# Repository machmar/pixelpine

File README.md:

# PixelPine — a 7 cm PCB Christmas tree with 240 charlieplexed LEDs

KTE Project 1 · design-for-manufacture study · rev A · 2026-09-23

A chubby, cute, 70 mm tall PCB tree covered in **240 warm-white 0603 LEDs** on a 2.12 mm grid. The LEDs are
charlieplexed on 16 pins of a **$0.13 Puya PY32F003** (Cortex-M0+, 64 KB flash) with software PWM. It runs from USB-C and slots into a
PCB stand fin. The tree is a character, **Pine**, whose job is showing light shows. He's bad at it: he daydreams,
naps, gets grumpy and gets excited to show you things. You interact with him through the capacitive star, which
senses tap, pet, press, a front-and-back squeeze and tickles. The product firmware runs on the first boards and
matches the simulator frame for frame ([`firmware/pixelpine/`](firmware/pixelpine/README.md)).
Landed cost ≈ **€3.2 at 1 000 pcs, €2.0 at 10 000 pcs**; suggested shelf price **€12.90**.

**Try Pine in your browser: [machmar.github.io/pixelpine](https://machmar.github.io/pixelpine/)** (the animation simulator).

| Front | Back |
|---|---|
|  |  |

## Deliverables

| You asked for | Where |
|---|---|
| Schematic | [`hardware/pixelpine_schematic.pdf`](hardware/pixelpine_schematic.pdf) · KiCad 10 project [`hardware/pixelpine.kicad_pro`](hardware/pixelpine.kicad_pro) (ERC: 0 errors, 0 warnings) |
| PCB shape and layout | [`hardware/pixelpine.kicad_pcb`](hardware/pixelpine.kicad_pcb): outline, stand fin, all 267 parts (+2 logo marks) placed with nets, silkscreen, CE/WEEE marks, **routed on 2 layers** (Freerouting, then finished by hand in KiCad: GND pour on both layers, 142 vias). DRC: 0 unconnected, schematic parity 0 issues; 2 cosmetic *starved thermal* notes (see the order guide). The LEDs sit in a routing-friendly arrangement: see [LED arrangement](#led-arrangement) |
| BOM (LCSC / JLCPCB) | [`docs/bom.md`](docs/bom.md) · JLC upload files [`hardware/production/jlc_bom.csv`](hardware/production/jlc_bom.csv), [`jlc_cpl.csv`](hardware/production/jlc_cpl.csv) |
| **Order files** | [`hardware/production/`](hardware/production/README.md): Gerber + drill zips for the tree (PCB + assembly) and the stand fin (bare PCB), BOM/CPL, 3D previews, and an order guide with every JLC setting and what to check in the placement preview |
| PC app to preview the animations | [`simulator/index.html`](simulator/index.html), live at [machmar.github.io/pixelpine](https://machmar.github.io/pixelpine/) (published from `simulator/` by `.github/workflows/pages.yml`): open it in any browser; works offline apart from fonts. Pine runs live: touch his star (hover / click / hold / shift / ctrl / fast clicks) and watch his feelings change. Preview mode plays any show, face or transition. Includes an electrical model of the charlieplex (current sag, PWM depth, refresh, pin current) |
| Pine: character, faces, transitions, gestures | [`docs/animations.md`](docs/animations.md): behaviour state machine, emotions, 15 light shows, 16 faces, 6 transitions, touch gestures, RAM/flash budget |
| Market analysis | [`docs/market-analysis.md`](docs/market-analysis.md) |
| EU certification setup | [`docs/eu-compliance/`](docs/eu-compliance/README.md): applicability matrix, EMC test plan, technical file + risk assessment, DoC template, labels and leaflet (EN/CZ) |
| Final price analysis incl. assembly | [`docs/cost-analysis.md`](docs/cost-analysis.md), generated by [`docs/cost_model.py`](docs/cost_model.py) |
| Connectivity & power consumption | [`docs/power-and-connectivity.md`](docs/power-and-connectivity.md) |
| Product firmware (beyond the brief) | [`firmware/pixelpine/`](firmware/pixelpine/README.md): the simulator ported to C and running on the board: **59 KB of 63 KB flash, 7.0 KB of 8 KB RAM**, 50 fps, 122 Hz 10-bit BCM scan. Checked frame by frame against the simulator's own JavaScript: Pine's state machine and emotions identical in every whole-Pine test, LED levels within 1 step of 255 on ≥ 99.99 % of LED-frames there (per show: 93–100 %, fireflies lowest). Touch calibrated on the board; room-light sensing isn't possible on rev A (and how rev B fixes it); a whole-tree touch field was tried and dropped (why). Flashing: [`firmware/flash/`](firmware/flash/README.md) |
| Firmware fit check | [`firmware/sizetest/`](firmware/sizetest/README.md): real compile of all shows, faces, brain and drivers for both MCUs. The original CH32V003 overflowed (20.9 KB of 16 KB), so the MCU was switched to the PY32F003F18P6: **17.2 KB of 64 KB flash (27 %), 1.9 KB of 8 KB RAM (23 %)**, built with the Arm GNU Toolchain. See [`docs/animations.md`](docs/animations.md#firmware-budget-measured-by-a-test-compile) |
| Design spec | [`docs/superpowers/specs/2026-09-23-pixelpine-design.md`](docs/superpowers/specs/2026-09-23-pixelpine-design.md) |
| All docs as PDF | [`docs/pdf/PixelPine-documentation.pdf`](docs/pdf/PixelPine-documentation.pdf): everything above in one linked PDF (cover, contents), plus one PDF per doc in [`docs/pdf/`](docs/pdf/). Regenerate with `python docs/export_pdfs.py` after editing a doc |

## Key numbers

| | |
|---|---|
| LEDs | 240 × XL-1608WWC-06 (0603, 2500–3000 K) at 45°, 2.12 mm pitch |
| MCU | Puya PY32F003F18P6 (TSSOP-20, pinout 1, 24 MHz internal oscillator): 16 charlieplex lines (incl. SWD pins and BOOT0) + ADC touch star (PA7) + NRST; SWD programming |
| Character | 6 emotions (energy, focus, mood, annoyance, excitement, bond in flash), 16 faces, 6 transitions |
| Parts | 263 placements, 8 line items, 552 SMD joints, single-sided |
| PCB | 2-layer FR-4 1.6 mm, LF-HASL, JLC standard process (0.10 mm tracks and spaces at the narrowest, 0.3 / 0.4 mm vias); 1658 track segments (1991 mm), 142 vias, GND pour on both layers, 0 unrouted. Tree 50.5 × 70 mm, stand fin 36 × 10 mm |
| Supply | USB-C 5 V, 3–12 mA typical (≈ 7 mA average), 19 mA max → ≤ 0.1 W |
| Light | ≈ 2 lm total, so outside the EU light-source ecodesign/energy-label scope |
| Pin current | ≤ 16.2 mA per GPIO by design (20 mA rated) |
| PWM | 8-bit binary-code modulation, 16 phases, 122 Hz refresh (the product firmware: 10-bit, same refresh) |
| CE route | EMC 2014/30/EU (EN IEC 55015 + EN 61547) + RoHS; GPSR, WEEE, PPWR, REACH obligations |

## LED arrangement

The 240 LED positions are a fixed 2.12 mm grid, but *which* anode/cathode pair sits at which position is a free choice,
and it decides whether the board can be routed at all. The first version interleaved the pairs (`anode = n mod 16`),
which leaves every one of the 480 LED pads as an island of its own, and Freerouting stalled with 76 connections still
open after 87 minutes.

The 45° LEDs form a "brick" lattice with only ~0.55 mm between neighbouring pads. If two neighbouring pads are on the
same line net, a tiny F.Cu bridge joins them for free, so a net can be a few big copper islands instead of 30 loose
pads. [`hardware/scripts/optimize_leds.py`](hardware/scripts/optimize_leds.py) (simulated annealing, C core in
`optimize_leds.c`) arranges the 240 pairs for exactly that: 480 separate pads became 141 islands, only the links between
islands need real wiring, and the board routes on **2 layers** in about 2 minutes (it also stopped needing the 4 layers
that the old arrangement was thought to need). The result is [`hardware/led_assignment.json`](hardware/led_assignment.json),
committed; `geometry.py` reads it, so the schematic, PCB, simulator map and firmware tables all follow from it. Every
LED keeps the same orientation; the optimiser can also turn LEDs round by 180° (`--flip`) for ~15 % fewer islands, but
that wasn't needed.

Side effect: neighbouring LEDs now sometimes share an anode line (17 % of the LED pairs closer than 3.2 mm, against
6 % with the old interleaving), so a lit blob loads some scan phases harder than before. The numbers are in
[`docs/power-and-connectivity.md`](docs/power-and-connectivity.md#which-leds-share-a-phase).

## Regenerating the hardware

> **Since 2026-10-01 the board is finished by hand in KiCad** (GND pour, extra vias). `build_all.py` would
> regenerate it from the scripts and drop those edits, so it now stops unless you pass `--regenerate`. For order
> files run `export_gerbers.py` (KiCad's Python) and `export_fab.py`; see
> [`hardware/production/README.md`](hardware/production/README.md).

Everything in `hardware/` was generated from one geometry module, so it stays consistent:

```bash
python hardware/scripts/build_all.py
```

`geometry.py` (outline, LED grid, charlieplex map from `led_assignment.json`) → `gen_footprints.py` → `gen_sch.py`
(+ ERC, netlist check) → `gen_pcb.py` (KiCad's bundled Python) → `route.py` (Freerouting, ~2-5 min; if connections stay
open it routes again from scratch, up to 4 runs) → DRC and parity → 3D renders → JLC BOM/CPL. It also refreshes
`simulator/led_map.js`, so the simulator always shows the real LED positions. After editing the outline, run
`python hardware/scripts/geometry.py --search` and paste the new pitch into `GRID_PITCH`, then
`python hardware/scripts/optimize_leds.py` (needs a C compiler, 10–20 min) to re-arrange the LEDs for the new grid.
The firmware's per-LED tables come from the same map: `python firmware/pixelpine/gen_tables.py`, then
`python firmware/pixelpine/build.py flash` builds and programs a board, and `python firmware/pixelpine/test/compare.py`
checks the firmware against the simulator.

## Open items before ordering

Order files are ready: [`hardware/production/README.md`](hardware/production/README.md). At order time, check
LCSC stock for the 240 LEDs per board and look at the LED polarity and U1 pin 1 in JLC's placement preview.

1. **Firmware: done on the first board** (2026-11-03): it powers up at 4.97 V with no short, flashes through a
   J-Link ([`firmware/flash/`](firmware/flash/README.md)) and runs Pine ([`firmware/pixelpine/`](firmware/pixelpine/README.md)).
   Still open: touch thresholds measured on one board and one hand (measure a batch); the EMC worst-case and
   production-test firmware builds.
2. **Room light can't be sensed on rev A**: in a full charlieplex every LED has an anti-parallel twin, so no LED can
   work as a photodiode, and Pine stays in "lights on" mode. Rev B fix at no cost: leave one LED unpopulated
   ([`firmware/pixelpine/README.md`](firmware/pixelpine/README.md#room-light)).
3. **Hover isn't detectable** with the star electrode (a finger 1 cm away is below the noise); tap, pet, press,
   squeeze and tickle work.
4. **No whole-tree touch on rev A**: the LED lines can pick up the mains hum a finger carries, but only on a
   mains-tied supply (strong on a laptop, weak on a wall charger, nothing on a powerbank), so it was dropped after
   five experiments ([`firmware/pixelpine/README.md`](firmware/pixelpine/README.md#touch-field-tried-dropped)). The star
   is the touch control.

Done: PCB routed on 2 layers (LED arrangement optimised for it, DRC clean), manufacturer name, address (Jehličková 240, 240 24 Stromečkov: made up for the school project, replace it with the
registered address for a real product) and e-mail on the product, U1 and J1 placement orientation checked, MCU choice final
(PY32F003F18P6, kept over the cheaper F002A for firmware-update headroom).

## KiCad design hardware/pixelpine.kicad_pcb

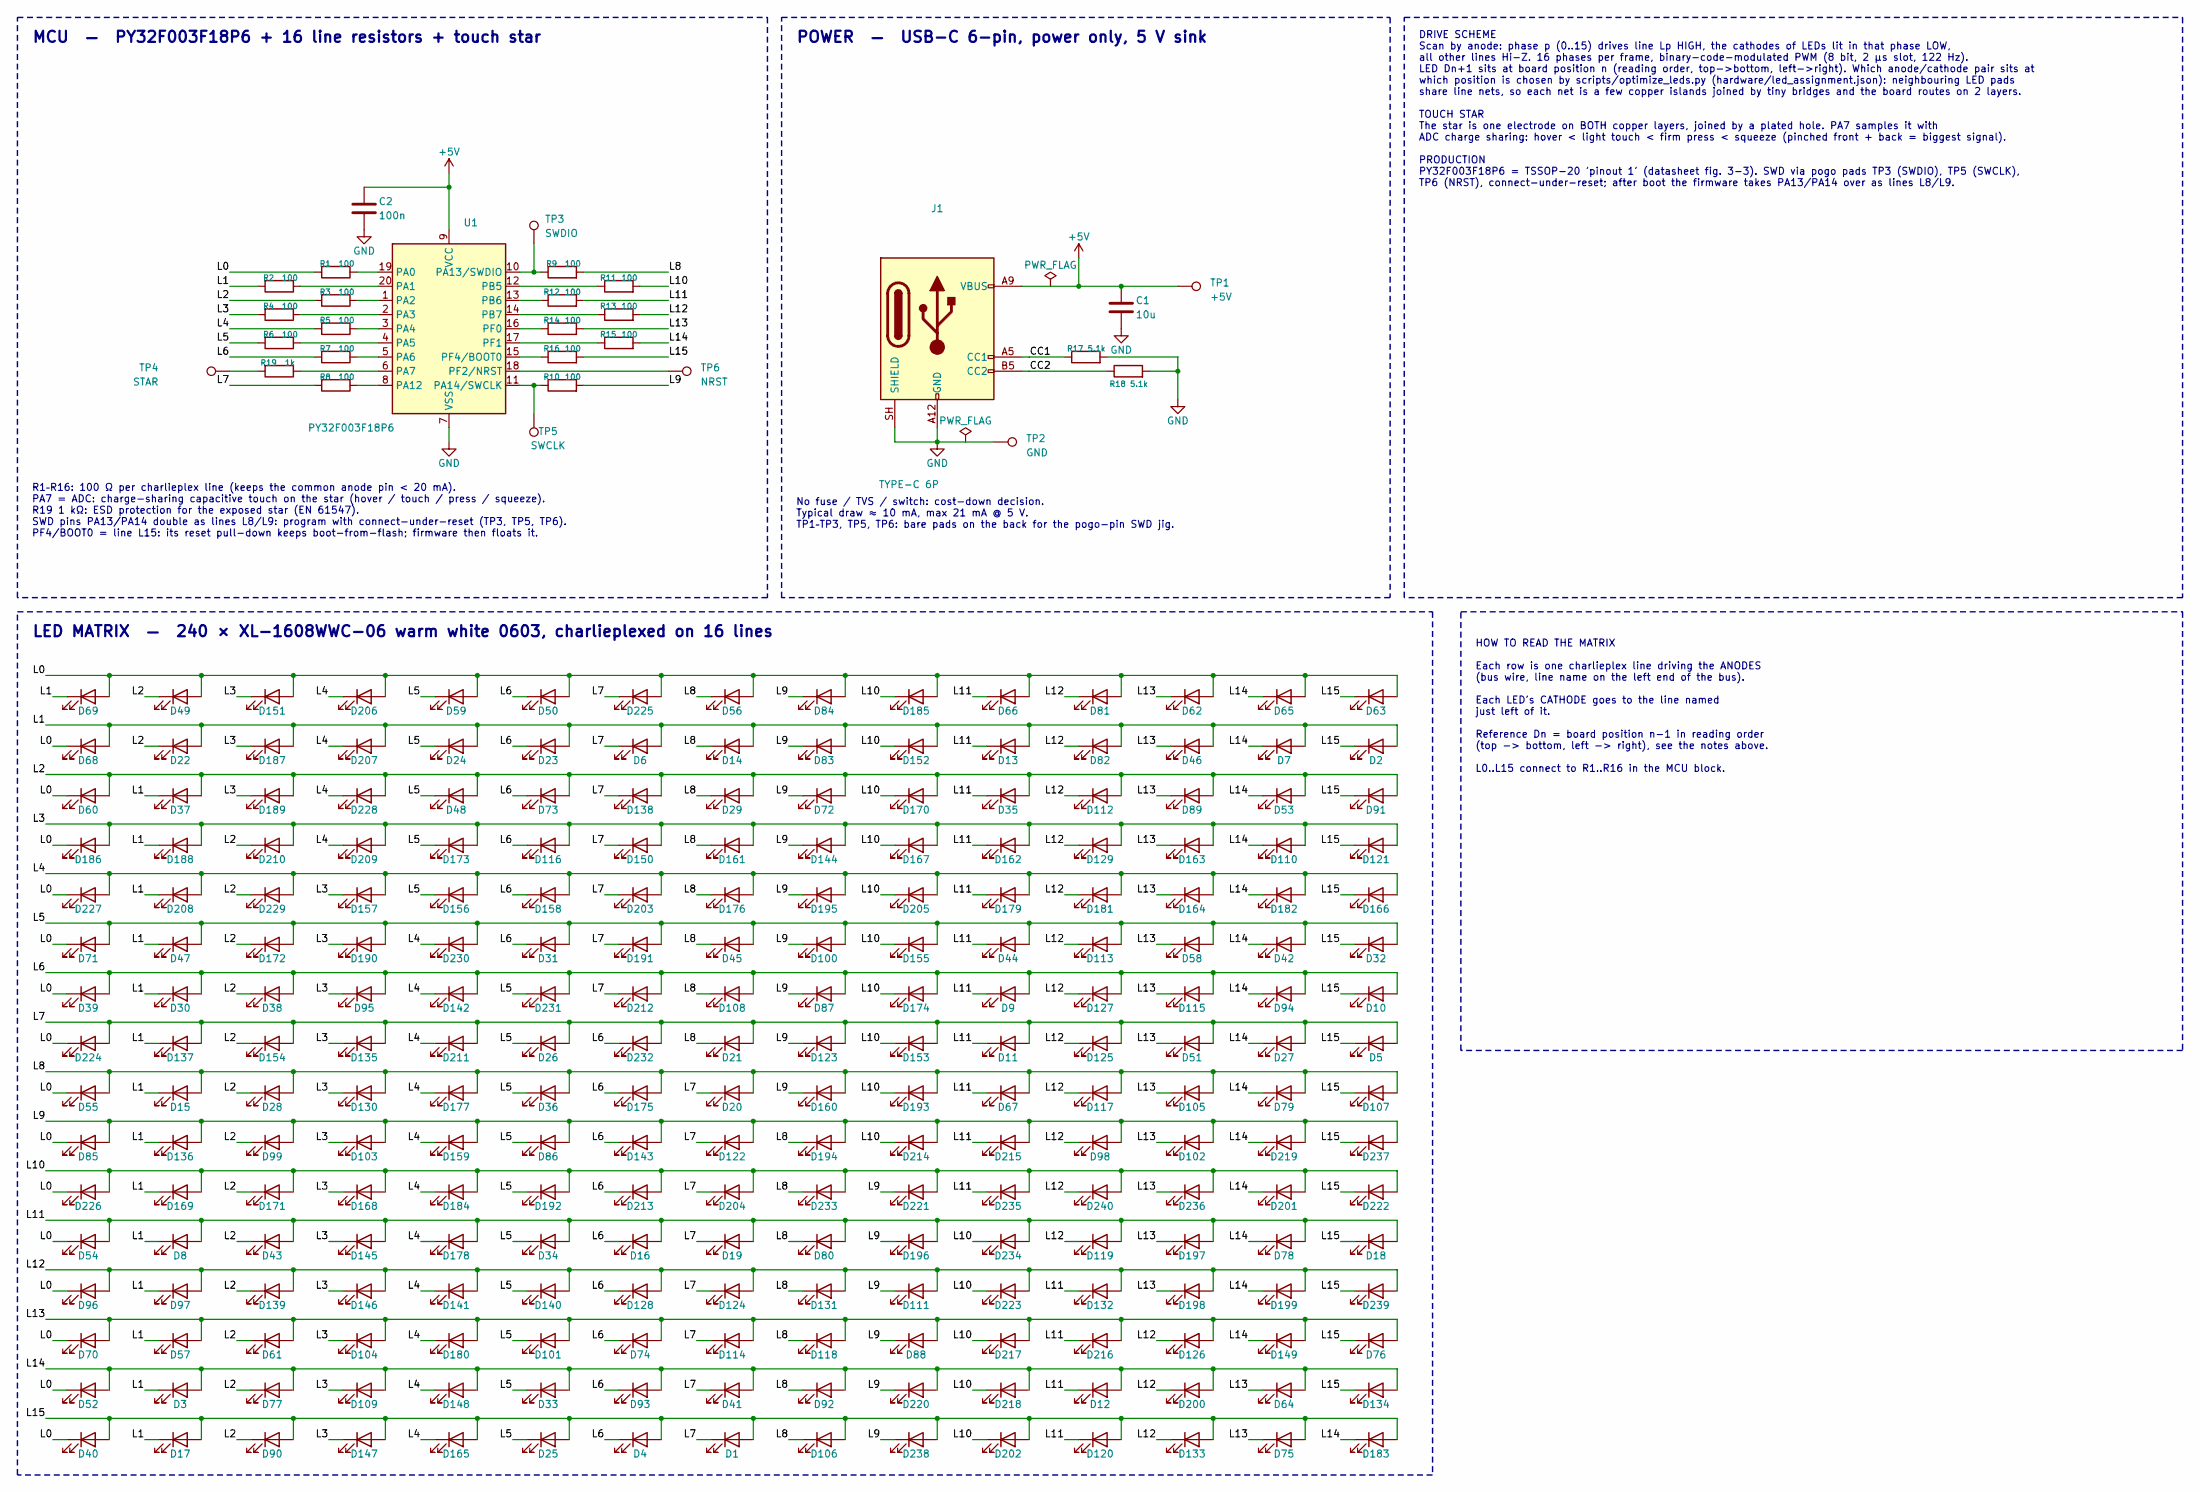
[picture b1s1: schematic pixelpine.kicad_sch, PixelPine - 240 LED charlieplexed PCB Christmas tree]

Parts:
C1: 10u; C_0603_1608Metric; LCSC C19702
C2: 100n; C_0402_1005Metric; LCSC C1525
D1, D2, D3, D4, D5, D6, D7, D8, D9, D10, D11, D12, D13, D14, D15, D16, D17, D18, D19, D20, D21, D22, D23, D24, D25, D26, D27, D28, D29, D30, D31, D32, D33, D34, D35, D36, D37, D38, D39, D40, D41, D42, D43, D44, D45, D46, D47, D48, D49, D50, D51, D52, D53, D54, D55, D56, D57, D58, D59, D60, D61, D62, D63, D64, D65, D66, D67, D68, D69, D70, D71, D72, D73, D74, D75, D76, D77, D78, D79, D80, D81, D82, D83, D84, D85, D86, D87, D88, D89, D90, D91, D92, D93, D94, D95, D96, D97, D98, D99, D100, D101, D102, D103, D104, D105, D106, D107, D108, D109, D110, D111, D112, D113, D114, D115, D116, D117, D118, D119, D120, D121, D122, D123, D124, D125, D126, D127, D128, D129, D130, D131, D132, D133, D134, D135, D136, D137, D138, D139, D140, D141, D142, D143, D144, D145, D146, D147, D148, D149, D150, D151, D152, D153, D154, D155, D156, D157, D158, D159, D160, D161, D162, D163, D164, D165, D166, D167, D168, D169, D170, D171, D172, D173, D174, D175, D176, D177, D178, D179, D180, D181, D182, D183, D184, D185, D186, D187, D188, D189, D190, D191, D192, D193, D194, D195, D196, D197, D198, D199, D200, D201, D202, D203, D204, D205, D206, D207, D208, D209, D210, D211, D212, D213, D214, D215, D216, D217, D218, D219, D220, D221, D222, D223, D224, D225, D226, D227, D228, D229, D230, D231, D232, D233, D234, D235, D236, D237, D238, D239, D240: XL-1608WWC-06; LED_0603_Dense; LCSC C965810
J1: TYPE-C 6P; USB_C_SHOUHAN_TYPE-C-6P; LCSC C456012
R1, R2, R3, R4, R5, R6, R7, R8, R9, R10, R11, R12, R13, R14, R15, R16: 100; R_0402_1005Metric; LCSC C25076
R17, R18: 5.1k; R_0402_1005Metric; LCSC C25905
R19: 1k; R_0402_1005Metric; LCSC C11702
TP1: +5V; TestPoint_Pad_D1.5mm
TP2: GND; TestPoint_Pad_D1.5mm
TP3: SWDIO; TestPoint_Pad_D1.5mm
TP4: STAR; TouchStar
TP5: SWCLK; TestPoint_Pad_D1.5mm
TP6: NRST; TestPoint_Pad_D1.5mm
U1: PY32F003F18P6; TSSOP-20_4.4x6.5mm_P0.65mm; LCSC C55338319

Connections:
+5V: C1.1, C2.1, J1.A9 (VBUS), J1.B9 (VBUS), TP1.1, U1.9 (VCC)
/CC1: J1.A5 (CC1), R17.1
/CC2: J1.B5 (CC2), R18.1
/L0: D39.1 (K), D40.1 (K), D49.2 (A), D50.2 (A), D52.1 (K), D54.1 (K), D55.1 (K), D56.2 (A), D59.2 (A), D60.1 (K), D62.2 (A), D63.2 (A), D65.2 (A), D66.2 (A), D68.1 (K), D69.2 (A), D70.1 (K), D71.1 (K), D81.2 (A), D84.2 (A), D85.1 (K), D96.1 (K), D151.2 (A), D185.2 (A), D186.1 (K), D206.2 (A), D224.1 (K), D225.2 (A), D226.1 (K), D227.1 (K), R1.2
/L1: D2.2 (A), D3.1 (K), D6.2 (A), D7.2 (A), D8.1 (K), D13.2 (A), D14.2 (A), D15.1 (K), D17.1 (K), D22.2 (A), D23.2 (A), D24.2 (A), D30.1 (K), D37.1 (K), D46.2 (A), D47.1 (K), D57.1 (K), D68.2 (A), D69.1 (K), D82.2 (A), D83.2 (A), D97.1 (K), D136.1 (K), D137.1 (K), D152.2 (A), D169.1 (K), D187.2 (A), D188.1 (K), D207.2 (A), D208.1 (K), R2.2
/L2: D22.1 (K), D28.1 (K), D29.2 (A), D35.2 (A), D37.2 (A), D38.1 (K), D43.1 (K), D48.2 (A), D49.1 (K), D53.2 (A), D60.2 (A), D61.1 (K), D72.2 (A), D73.2 (A), D77.1 (K), D89.2 (A), D90.1 (K), D91.2 (A), D99.1 (K), D112.2 (A), D138.2 (A), D139.1 (K), D154.1 (K), D170.2 (A), D171.1 (K), D172.1 (K), D189.2 (A), D210.1 (K), D228.2 (A), D229.1 (K), R3.2
/L3: D95.1 (K), D103.1 (K), D104.1 (K), D109.1 (K), D110.2 (A), D116.2 (A), D121.2 (A), D129.2 (A), D130.1 (K), D135.1 (K), D144.2 (A), D145.1 (K), D146.1 (K), D147.1 (K), D150.2 (A), D151.1 (K), D157.1 (K), D161.2 (A), D162.2 (A), D163.2 (A), D167.2 (A), D168.1 (K), D173.2 (A), D186.2 (A), D187.1 (K), D188.2 (A), D189.1 (K), D190.1 (K), D209.2 (A), D210.2 (A), R4.2
/L4: D141.1 (K), D142.1 (K), D148.1 (K), D156.2 (A), D157.2 (A), D158.2 (A), D159.1 (K), D164.2 (A), D165.1 (K), D166.2 (A), D176.2 (A), D177.1 (K), D178.1 (K), D179.2 (A), D180.1 (K), D181.2 (A), D182.2 (A), D184.1 (K), D195.2 (A), D203.2 (A), D205.2 (A), D206.1 (K), D207.1 (K), D208.2 (A), D209.1 (K), D211.1 (K), D227.2 (A), D228.1 (K), D229.2 (A), D230.1 (K), R5.2
/L5: D24.1 (K), D25.1 (K), D26.1 (K), D31.2 (A), D32.2 (A), D33.1 (K), D34.1 (K), D36.1 (K), D42.2 (A), D44.2 (A), D45.2 (A), D47.2 (A), D48.1 (K), D58.2 (A), D59.1 (K), D71.2 (A), D86.1 (K), D100.2 (A), D101.1 (K), D113.2 (A), D140.1 (K), D155.2 (A), D156.1 (K), D172.2 (A), D173.1 (K), D190.2 (A), D191.2 (A), D192.1 (K), D230.2 (A), D231.1 (K), R6.2
/L6: D4.1 (K), D9.2 (A), D10.2 (A), D16.1 (K), D23.1 (K), D30.2 (A), D31.1 (K), D38.2 (A), D39.2 (A), D50.1 (K), D73.1 (K), D74.1 (K), D87.2 (A), D93.1 (K), D94.2 (A), D95.2 (A), D108.2 (A), D115.2 (A), D116.1 (K), D127.2 (A), D128.1 (K), D142.2 (A), D143.1 (K), D158.1 (K), D174.2 (A), D175.1 (K), D212.2 (A), D213.1 (K), D231.2 (A), D232.1 (K), R7.2
/L7: D1.1 (K), D5.2 (A), D6.1 (K), D11.2 (A), D19.1 (K), D20.1 (K), D21.2 (A), D26.2 (A), D27.2 (A), D41.1 (K), D51.2 (A), D114.1 (K), D122.1 (K), D123.2 (A), D124.1 (K), D125.2 (A), D135.2 (A), D137.2 (A), D138.1 (K), D150.1 (K), D153.2 (A), D154.2 (A), D191.1 (K), D203.1 (K), D204.1 (K), D211.2 (A), D212.1 (K), D224.2 (A), D225.1 (K), D232.2 (A), R8.2
/L8: D14.1 (K), D15.2 (A), D20.2 (A), D21.1 (K), D28.2 (A), D29.1 (K), D36.2 (A), D45.1 (K), D55.2 (A), D56.1 (K), D67.2 (A), D79.2 (A), D80.1 (K), D92.1 (K), D105.2 (A), D106.1 (K), D107.2 (A), D108.1 (K), D117.2 (A), D118.1 (K), D130.2 (A), D131.1 (K), D160.2 (A), D161.1 (K), D175.2 (A), D176.1 (K), D177.2 (A), D193.2 (A), D194.1 (K), D233.1 (K), R9.2
/L9: D72.1 (K), D83.1 (K), D84.1 (K), D85.2 (A), D86.2 (A), D87.1 (K), D88.1 (K), D98.2 (A), D99.2 (A), D100.1 (K), D102.2 (A), D103.2 (A), D111.1 (K), D122.2 (A), D123.1 (K), D136.2 (A), D143.2 (A), D144.1 (K), D159.2 (A), D160.1 (K), D194.2 (A), D195.1 (K), D196.1 (K), D214.2 (A), D215.2 (A), D219.2 (A), D220.1 (K), D221.1 (K), D237.2 (A), D238.1 (K), R10.2
/L10: D152.1 (K), D153.1 (K), D155.1 (K), D167.1 (K), D168.2 (A), D169.2 (A), D170.1 (K), D171.2 (A), D174.1 (K), D184.2 (A), D185.1 (K), D192.2 (A), D193.1 (K), D201.2 (A), D202.1 (K), D204.2 (A), D205.1 (K), D213.2 (A), D214.1 (K), D217.1 (K), D218.1 (K), D221.2 (A), D222.2 (A), D223.1 (K), D226.2 (A), D233.2 (A), D234.1 (K), D235.2 (A), D236.2 (A), D240.2 (A), R11.2
/L11: D8.2 (A), D9.1 (K), D11.1 (K), D12.1 (K), D13.1 (K), D16.2 (A), D18.2 (A), D19.2 (A), D34.2 (A), D35.1 (K), D43.2 (A), D44.1 (K), D54.2 (A), D66.1 (K), D67.1 (K), D78.2 (A), D80.2 (A), D119.2 (A), D120.1 (K), D132.1 (K), D145.2 (A), D162.1 (K), D178.2 (A), D179.1 (K), D196.2 (A), D197.2 (A), D215.1 (K), D216.1 (K), D234.2 (A), D235.1 (K), R12.2
/L12: D81.1 (K), D82.1 (K), D96.2 (A), D97.2 (A), D98.1 (K), D111.2 (A), D112.1 (K), D113.1 (K), D117.1 (K), D119.1 (K), D124.2 (A), D125.1 (K), D126.1 (K), D127.1 (K), D128.2 (A), D129.1 (K), D131.2 (A), D132.2 (A), D133.1 (K), D139.2 (A), D140.2 (A), D141.2 (A), D146.2 (A), D181.1 (K), D198.2 (A), D199.2 (A), D200.1 (K), D223.2 (A), D239.2 (A), D240.1 (K), R13.2
/L13: D46.1 (K), D51.1 (K), D57.2 (A), D58.1 (K), D61.2 (A), D62.1 (K), D64.1 (K), D70.2 (A), D74.2 (A), D75.1 (K), D76.2 (A), D88.2 (A), D89.1 (K), D101.2 (A), D102.1 (K), D104.2 (A), D105.1 (K), D114.2 (A), D115.1 (K), D118.2 (A), D126.2 (A), D149.2 (A), D163.1 (K), D164.1 (K), D180.2 (A), D197.1 (K), D198.1 (K), D216.2 (A), D217.2 (A), D236.1 (K), R14.2
/L14: D3.2 (A), D7.1 (K), D12.2 (A), D27.1 (K), D33.2 (A), D41.2 (A), D42.1 (K), D52.2 (A), D53.1 (K), D64.2 (A), D65.1 (K), D77.2 (A), D78.1 (K), D79.1 (K), D92.2 (A), D93.2 (A), D94.1 (K), D109.2 (A), D110.1 (K), D134.2 (A), D148.2 (A), D149.1 (K), D182.1 (K), D183.1 (K), D199.1 (K), D200.2 (A), D201.1 (K), D218.2 (A), D219.1 (K), D220.2 (A), R15.2
/L15: D1.2 (A), D2.1 (K), D4.2 (A), D5.1 (K), D10.1 (K), D17.2 (A), D18.1 (K), D25.2 (A), D32.1 (K), D40.2 (A), D63.1 (K), D75.2 (A), D76.1 (K), D90.2 (A), D91.1 (K), D106.2 (A), D107.1 (K), D120.2 (A), D121.1 (K), D133.2 (A), D134.1 (K), D147.2 (A), D165.2 (A), D166.1 (K), D183.2 (A), D202.2 (A), D222.1 (K), D237.1 (K), D238.2 (A), D239.1 (K), R16.2
GND: C1.2, C2.2, J1.A12 (GND), J1.B12 (GND), J1.SH (SHIELD), R17.2, R18.2, TP2.1, U1.7 (VSS)
unnamed: R19.2, TP4.1
unnamed: R1.1, U1.19 (PA0)
unnamed: R2.1, U1.20 (PA1)
unnamed: R3.1, U1.1 (PA2)
unnamed: R4.1, U1.2 (PA3)
unnamed: R5.1, U1.3 (PA4)
unnamed: R6.1, U1.4 (PA5)
unnamed: R7.1, U1.5 (PA6)
unnamed: R19.1, U1.6 (PA7)
unnamed: R8.1, U1.8 (PA12)
unnamed: R9.1, TP3.1, U1.10 (PA13/SWDIO)
unnamed: R10.1, TP5.1, U1.11 (PA14/SWCLK)
unnamed: R11.1, U1.12 (PB5)
unnamed: R12.1, U1.13 (PB6)
unnamed: R13.1, U1.14 (PB7)
unnamed: R14.1, U1.16 (PF0)
unnamed: R15.1, U1.17 (PF1)
unnamed: TP6.1, U1.18 (PF2/NRST)
unnamed: R16.1, U1.15 (PF4/BOOT0)

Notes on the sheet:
MCU — PY32F003F18P6 + 16 line resistors + touch star
R1–R16: 100 Ω per charlieplex line (keeps the common anode pin < 20 mA). PA7 = ADC: charge-sharing capacitive touch on the star (hover / touch / press / squeeze). R19 1 kΩ: ESD protection for the exposed star (EN 61547). SWD pins PA13/PA14 double as lines L8/L9: program with connect-under-reset (TP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
POWER — USB-C 6-pin, power only, 5 V sink
No fuse / TVS / switch: cost-down decision. Typical draw ≈ 10 mA, max 21 mA @ 5 V. TP1–TP3, TP5, TP6: bare pads on the back for the pogo-pin SWD jig.
DRIVE SCHEME Scan by anode: phase p (0..15) drives line Lp HIGH, the cathodes of LEDs lit in that phase LOW, all other lines Hi-Z. 16 phases per frame, binary-code-modulated PWM (8 bit, 2 µs slot, 122 Hz). LED Dn+1 sits at board position n (reading order, top->bottom, left->right). Which anode/cath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
LED MATRIX — 240 × XL-1608WWC-06 warm white 0603, charlieplexed on 16 lines
HOW TO READ THE MATRIX Each row is one charlieplex line driving the ANODES (bus wire, line name on the left end of the bus). Each LED's CATHODE goes to the line named just left of it. Reference Dn = board position n-1 in reading order (top -> bottom, left -> right), see the notes above. L0..L15 con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

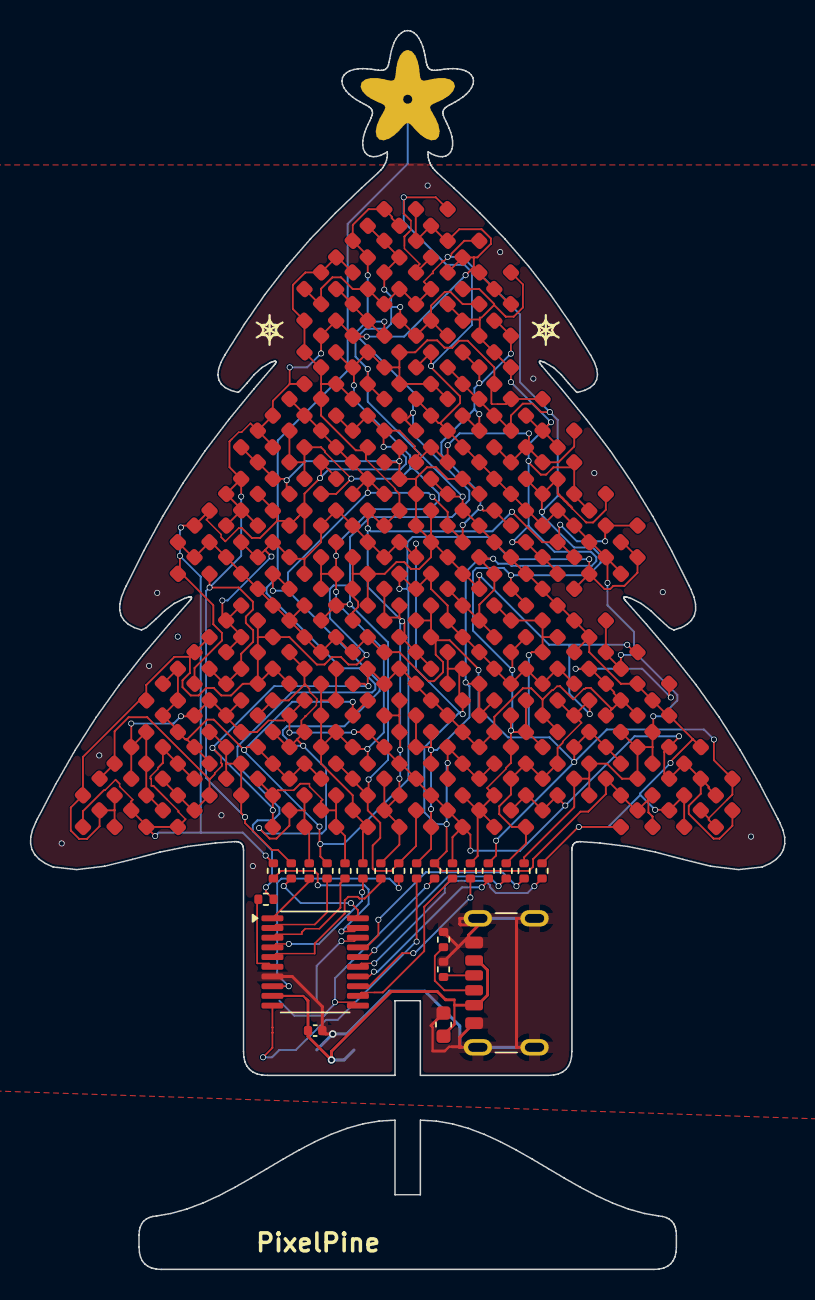
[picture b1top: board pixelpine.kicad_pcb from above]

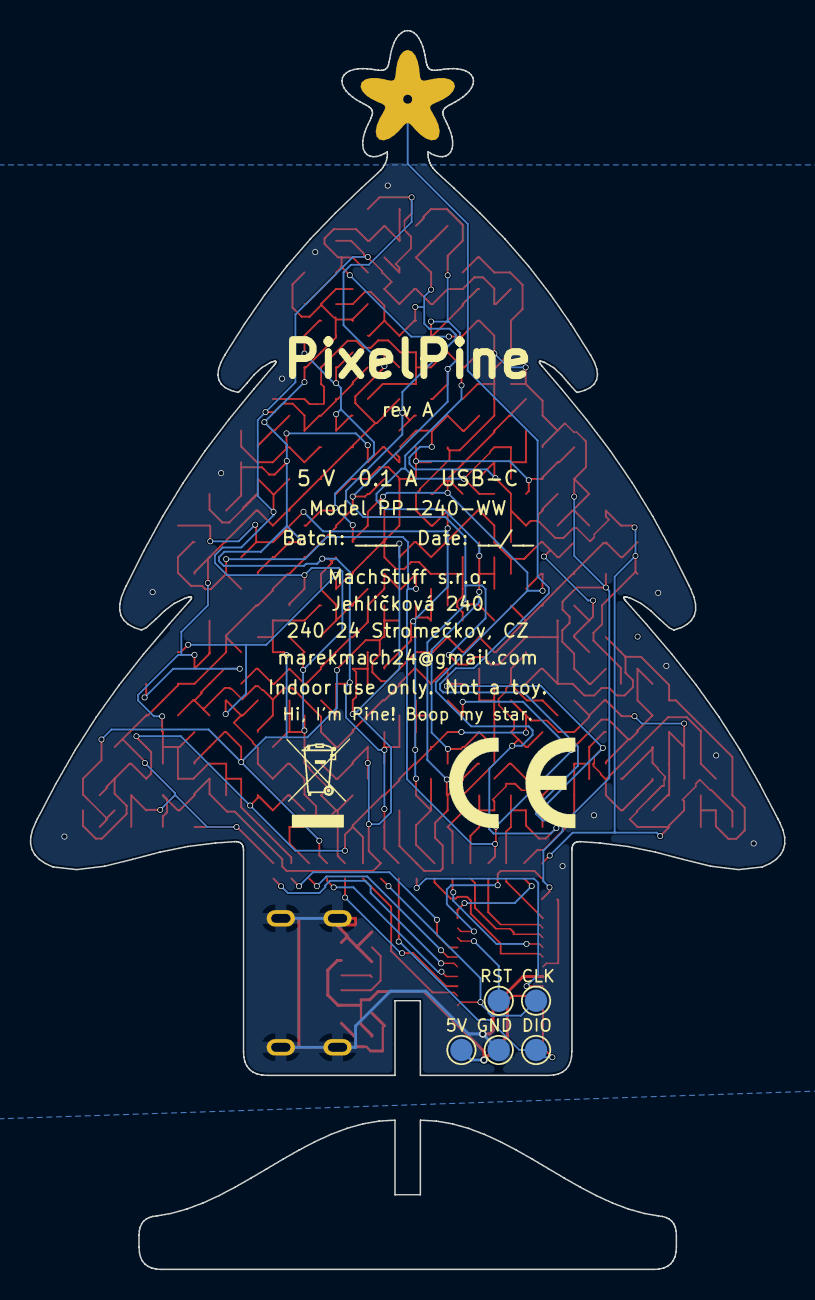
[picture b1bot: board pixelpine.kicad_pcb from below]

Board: 2 copper layers, 50.5 x 83.0 mm, 271 parts (7 on the bottom side), 39 nets.

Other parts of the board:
LOGO1: CE-Logo_8.5x6mm_SilkScreen
LOGO2: WEEE-Logo_4.2x6mm_SilkScreen

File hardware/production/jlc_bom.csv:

Comment,Designator,Footprint,LCSC Part #,Qty
XL-1608WWC-06,"D1,D2,D3,D4,D5,D6,D7,D8,D9,D10,D11,D12,D13,D14,D15,D16,D17,D18,D19,D20,D21,D22,D23,D24,D25,D26,D27,D28,D29,D30,D31,D32,D33,D34,D35,D36,D37,D38,D39,D40,D41,D42,D43,D44,D45,D46,D47,D48,D49,D50,D51,D52,D53,D54,D55,D56,D57,D58,D59,D60,D61,D62,D63,D64,D65,D66,D67,D68,D69,D70,D71,D72,D73,D74,D75,D76,D77,D78,D79,D80,D81,D82,D83,D84,D85,D86,D87,D88,D89,D90,D91,D92,D93,D94,D95,D96,D97,D98,D99,D100,D101,D102,D103,D104,D105,D106,D107,D108,D109,D110,D111,D112,D113,D114,D115,D116,D117,D118,D119,D120,D121,D122,D123,D124,D125,D126,D127,D128,D129,D130,D131,D132,D133,D134,D135,D136,D137,D138,D139,D140,D141,D142,D143,D144,D145,D146,D147,D148,D149,D150,D151,D152,D153,D154,D155,D156,D157,D158,D159,D160,D161,D162,D163,D164,D165,D166,D167,D168,D169,D170,D171,D172,D173,D174,D175,D176,D177,D178,D179,D180,D181,D182,D183,D184,D185,D186,D187,D188,D189,D190,D191,D192,D193,D194,D195,D196,D197,D198,D199,D200,D201,D202,D203,D204,D205,D206,D207,D208,D209,D210,D211,D212,D213,D214,D215,D216,D217,D218,D219,D220,D221,D222,D223,D224,D225,D226,D227,D228,D229,D230,D231,D232,D233,D234,D235,D236,D237,D238,D239,D240",LED_0603_Dense,C965810,240
100,"R1,R2,R3,R4,R5,R6,R7,R8,R9,R10,R11,R12,R13,R14,R15,R16",R_0402_1005Metric,C25076,16
5.1k,"R17,R18",R_0402_1005Metric,C25905,2
10u,C1,C_0603_1608Metric,C19702,1
100n,C2,C_0402_1005Metric,C1525,1
TYPE-C 6P,J1,USB_C_SHOUHAN_TYPE-C-6P,C456012,1
1k,R19,R_0402_1005Metric,C11702,1
PY32F003F18P6,U1,TSSOP-20_4.4x6.5mm_P0.65mm,C55338319,1

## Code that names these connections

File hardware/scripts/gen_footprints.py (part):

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# PY32F003F18P6, TSSOP-20 "Pinout 1" (datasheet Rev 1.7, figure 3-3: PY32F003F1xPx). KiCad ships no PY32F003 symbol,
# and the F002A symbol has a different pinout. (name, number, type, side, row) - rows count down from the top.
PY32_PINS = [
    ("PA0", 19, "bidirectional", "L", 0), ("PA1", 20, "bidirectional", "L", 1), ("PA2", 1, "bidirectional", "L", 2),
    ("PA3", 2, "bidirectional", "L", 3), ("PA4", 3, "bidirectional", "L", 4), ("PA5", 4, "bidirectional", "L", 5),
    ("PA6", 5, "bidirectional", "L", 6), ("PA7", 6, "bidirectional", "L", 7), ("PA12", 8, "bidirectional", "L", 8),
    ("PA13/SWDIO", 10, "bidirectional", "R", 0),                          # SWD pins top + bottom: room for pads
    ("PB5", 12, "bidirectional", "R", 1), ("PB6", 13, "bidirectional", "R", 2), ("PB7", 14, "bidirectional", "R", 3),
    ("PF0", 16, "bidirectional", "R", 4), ("PF1", 17, "bidirectional", "R", 5), ("PF4/BOOT0", 15, "bidirectional", "R", 6),
    ("PF2/NRST", 18, "bidirectional", "R", 7), ("PA14/SWCLK", 11, "bidirectional", "R", 8),
    ("VCC", 9, "power_in", "T", 0), ("VSS", 7, "power_in", "B", 0),
]

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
